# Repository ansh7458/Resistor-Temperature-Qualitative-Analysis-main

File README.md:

# 🌡️ Qualitative Analysis of Resistor's Temperature Behaviour

> **Centre for Electronic Design and Technology**  
> Netaji Subhas University of Technology, New Delhi  
> *Date: February 2024*

---

## 📋 Table of Contents
- [Synopsis](#-synopsis)
- [Introduction](#-introduction)
- [Procedure](#-procedure)
- [Results](#-results)
- [Conclusion](#-conclusion)
- [Bill of Materials](#-bill-of-materials)

---

## 🎯 Synopsis

This experiment provides a **qualitative investigation** of how standard resistor values change with temperature. Using a controlled heating setup and an Arduino-based measurement system with a K-type thermocouple (MAX6675), the resistance variation was monitored as the resistor was heated. The results provide visual and empirical evidence of the temperature-dependent behavior of resistive components.

## 📖 Introduction

Resistor values are not constant — they change with temperature. This temperature dependence is an important consideration in precision circuit design. By heating a resistor in a controlled manner and simultaneously measuring both its resistance and temperature, we can observe and characterize this behavior qualitatively.

## ⚙️ Procedure

1. Test resistor placed in a heated cavity (wire-wound power resistor)
2. K-type thermocouple (MAX6675) monitored temperature
3. Resistance measured via voltage divider with Arduino
4. Data logged via serial to CSV using CoolTerm
5. Results analyzed and plotted in Python

## 📊 Results

The resistance–temperature plot clearly shows the expected trend: resistance decreases with increasing temperature for the tested carbon-composition resistors.

## ✅ Conclusion

The experiment successfully demonstrated the qualitative relationship between temperature and resistance, providing visual evidence that supports the theoretical understanding of negative TCR behavior in standard carbon-composition resistors.

## 📦 Bill of Materials

| S.No | Component | Value | Qty |
|------|-----------|-------|-----|
| 1 | Test Resistor | Various | 1 |
| 2 | Power Resistor | 5 Ω (35W) | 1 |
| 3 | Arduino Uno | — | 1 |
| 4 | Thermocouple (MAX6675) | K-type | 1 |
| 5 | DC Power Supply | — | 1 |

## 🛠️ Technologies Used

`Arduino` · `Python` · `MAX6675` · `CoolTerm` · `Matplotlib`

## 👥 Authors
- **Ansh Gupta** — NSUT, New Delhi
- **Shubham Kumar** — NSUT, New Delhi

---
*Centre for Electronic Design and Technology, NSUT, New Delhi*

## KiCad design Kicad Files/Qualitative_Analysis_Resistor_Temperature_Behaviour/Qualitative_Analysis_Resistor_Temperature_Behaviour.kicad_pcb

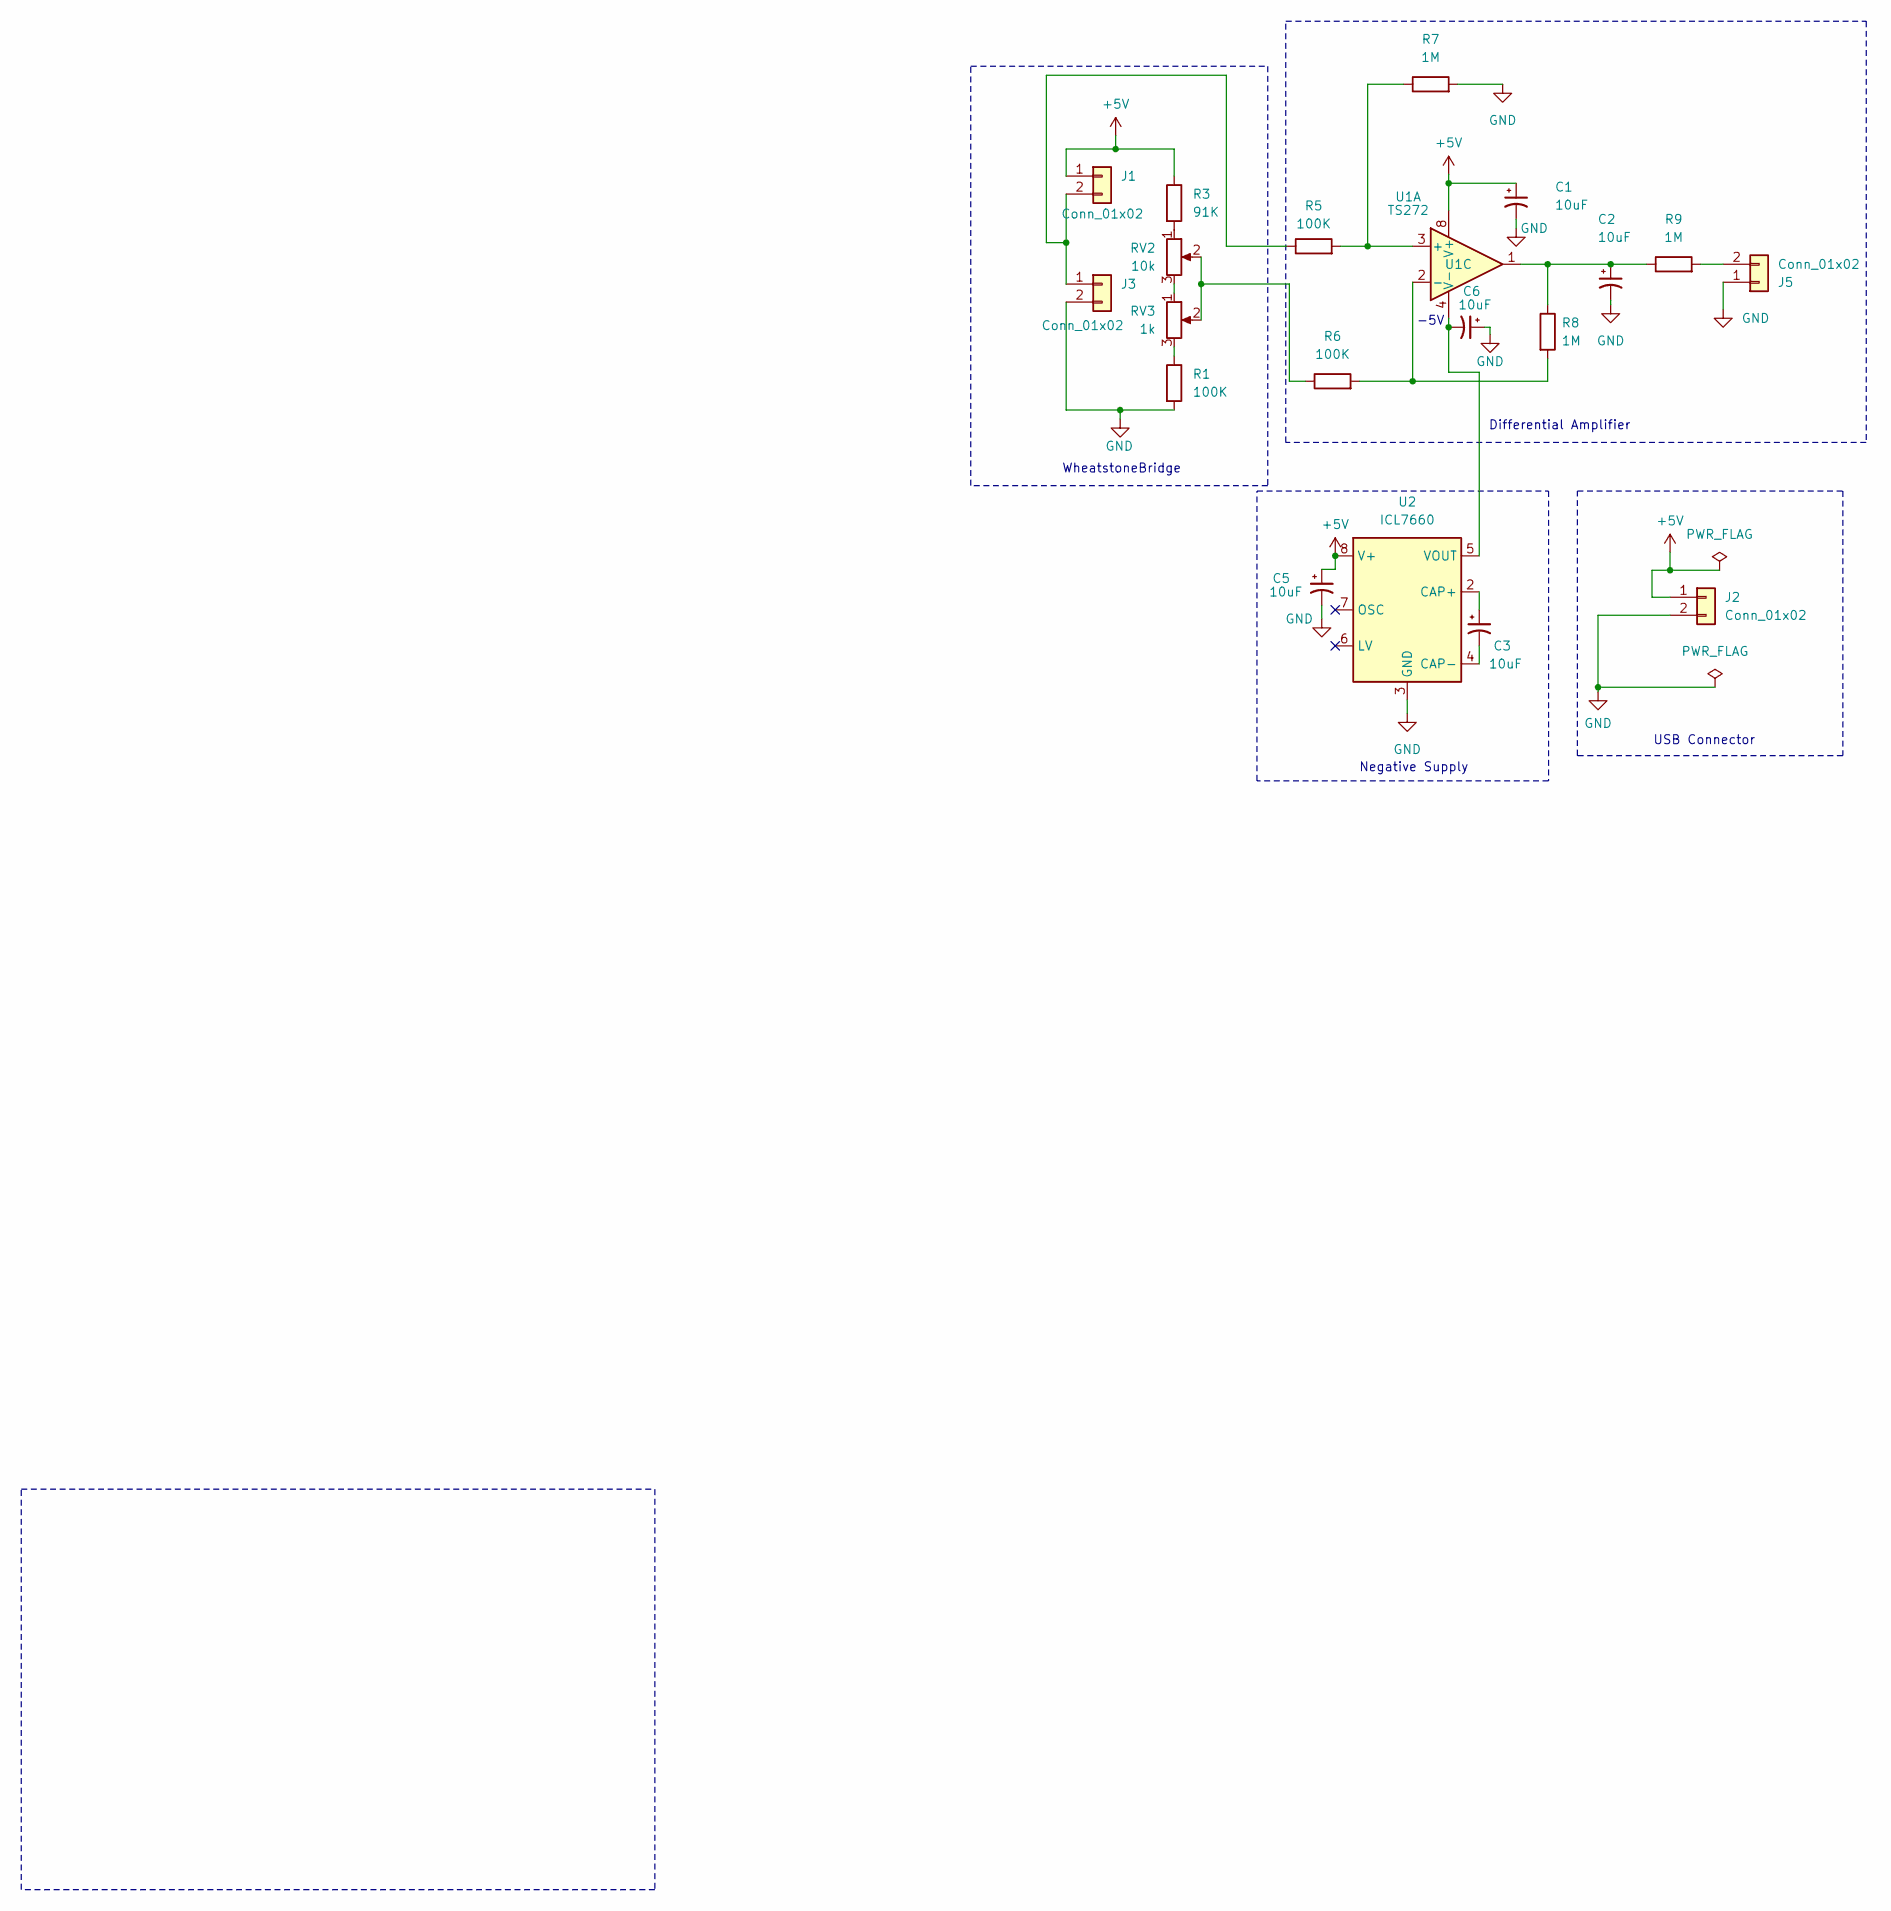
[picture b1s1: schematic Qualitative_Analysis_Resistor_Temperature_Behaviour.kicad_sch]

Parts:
C1, C2, C3, C5, C6: 10uF; CP_Radial_D5.0mm_P2.50mm
J1, J2, J3, J5: Conn_01x02; JST_EH_B2B-EH-A_1x02_P2.50mm_Vertical
R1, R5, R6: 100K; R_Axial_DIN0207_L6.3mm_D2.5mm_P15.24mm_Horizontal
R3: 91K; R_Axial_DIN0207_L6.3mm_D2.5mm_P15.24mm_Horizontal
R7, R8, R9: 1M; R_Axial_DIN0207_L6.3mm_D2.5mm_P15.24mm_Horizontal
RV2: 10k; JST_EH_B3B-EH-A_1x03_P2.50mm_Vertical
RV3: 1k; JST_EH_B3B-EH-A_1x03_P2.50mm_Vertical
U1: TS272; DIP-8_W7.62mm
U2: ICL7660; DIP-8_W7.62mm

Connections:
+5V: C1.1, C5.1, J1.1, J2.1, R3.1, U1.8 (V+), U2.8 (V+)
-5V: C6.2, U1.4 (V-), U2.5 (VOUT)
/i/o1: J1.2, J3.1, R5.1
/i/o2: R6.1, RV2.2, RV3.2
GND: C1.2, C2.2, C5.2, C6.1, J2.2, J3.2, J5.1, R1.2, R7.2, U2.3 (GND)
unnamed: C2.1, R8.1, R9.1, U1.1
unnamed: J5.2, R9.2
unnamed: R1.1, RV3.3
unnamed: R3.2, RV2.1
unnamed: RV2.3, RV3.1
unnamed: R5.2, R7.1, U1.3 (+)
unnamed: R6.2, R8.2, U1.2 (-)
unnamed: C3.1, U2.2 (CAP+)
unnamed: C3.2, U2.4 (CAP-)

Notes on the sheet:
-5V
Differential Amplifier
USB Connector
WheatstoneBridge
Negative Supply

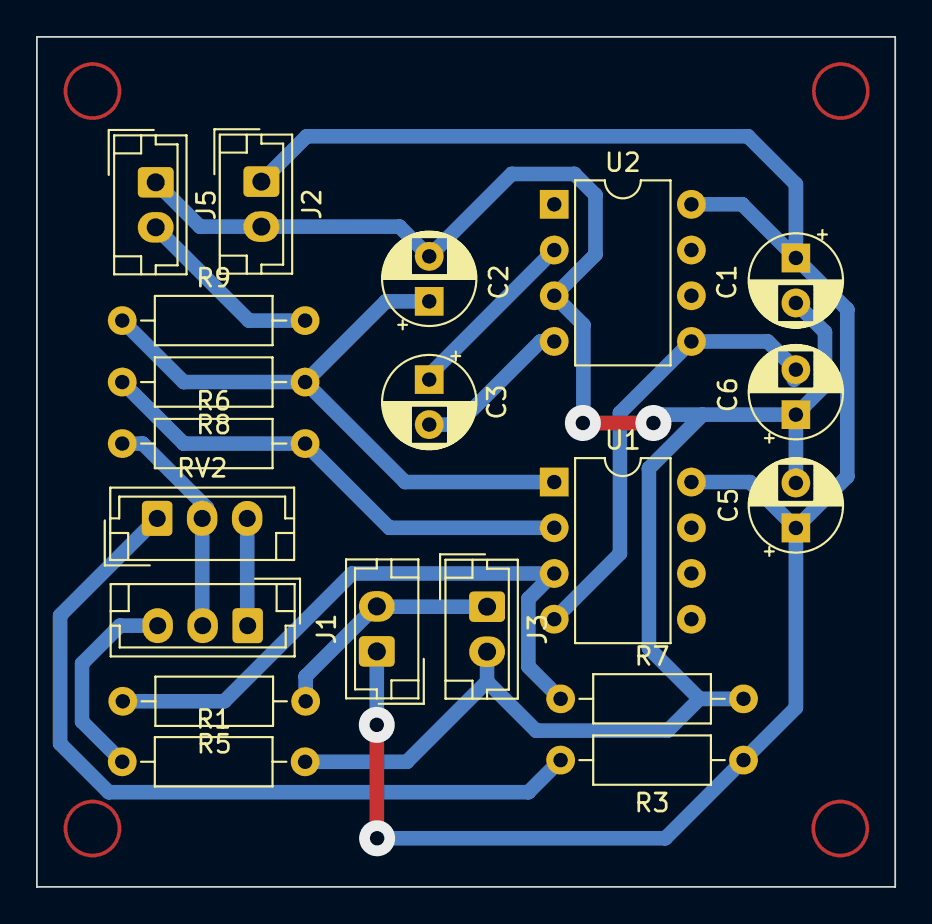
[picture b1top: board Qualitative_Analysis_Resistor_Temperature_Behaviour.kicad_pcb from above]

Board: 2 copper layers, 47.7 x 47.2 mm, 20 parts (0 on the bottom side), 14 nets.
